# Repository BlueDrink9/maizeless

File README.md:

# Maizeless

Maizeless is a split, wireless-only, choc-spaced, diodeless mechanical keyboard, for use with the much-cheaper nice!nano clone, the [SuperMini nrf52840](https://wiki.icbbuy.com/doku.php?id=developmentboard:nrf52840).

## Lineage

Maizeless is closely related to the [Corne](https://github.com/foostan/crkbd), but without the maze of a row and column diodes (hence the name). Probably the closest description of it is a wireless [Cantor](https://github.com/diepala/cantor) (AirCantor, if you will?), or a diodeless [Swept Corne](https://github.com/AYM1607/swept-crkbd).

Going from matrix+diodes to direct pin was only possible with the extra 3 pins of the nice!nano (and clones) and giving up the TRRS pin, so this board is wireless only.

Genealogically speaking, it is forked from the [temper](https://github.com/raeedcho/temper), owing its starting shape and schematic to those pcb files. 

## Features

- 42-key split keyboard with 3 rows x 6 columns + 3 thumb keys per half 
- No diodes
- Kailh choc spacing
- Sweep-like column stagger (with pinky columns 2 mm lower, like chocofi) with Corne-like thumb cluster
- Reversible PCB (so one design can be used for both halves)
- Intended to be used with [SuperMini nrf52840](https://wiki.icbbuy.com/doku.php?id=developmentboard:nrf52840)
- Uses a dirt-cheap 3-pin [SS12D00 SPDT power switch](https://vimex.com/switches/techdocs/SS12D00-tech.pdf), of which dozens of cheap clones are available on aliexpress.
- Includes pads for battery wires on the keyboard shield PCB, and through-holes if you prefer to solder that way.
- Easy and cheap to assemble, no soldering diodes and only through-hole
  soldering.
- (non-feature) - awkward battery positioning, and no easy JST plug spot for the battery. Not a big deal, just a heads up if you care, but I figure if you're here you're happy desoldering two wires to remove a battery. The off-switch will keep the power disconnected when not in use/travelling, anyway.
- Trivial to alter the PCB design for:
  * 5 columns
  * use real nice!nanos (the 3 extra pins are in a sliiightly different position compared to the supermini).
  * Kailh hotswap sockets in the PCB design, if you'd rather solder those to pads instead of direct through-hole soldering switches.

## Bill of Materials

- PCB x2
- 2x SuperMini nrf52840 microcontrollers
- 2x LiPo batteries (see nice!nano documentation for suggestions)
- 2x SS12D00 SPDT switches
- 42x Kailh choc v1 switches
- 42x Choc v1 keycaps
- (optional) MCU socket (more of a hassle than usual because we're
  using the extra 3 pins):
  - 4x Mill-Max 310 series machine sockets
  - 54x Mill-Max pins for socketing microcontrollers
- (optional) 2x Panasonic miniature momentary button switches  (for convenient reset buttons)

## Assembly

Assembly of this keyboard requires soldering the jumpers on the front-side of each PCB (underneath the microcontrollers). Past this, the assembly of this keyboard is similar to that of many other split wireless keyboards--there are many guides online to help. Briefly, the full list of steps includes:

- Solder the jumpers underneath the microcontrollers
- On PCB back:
  - Solder the diodes (ensuring diodes are oriented correctly--check diode schematic to match orientation to PCB)
  - Solder the switch sockets
- On PCB front:
  - Solder reset switch
  - Solder power switch
  - [Socket microcontroller](https://docs.splitkb.com/hc/en-us/articles/360011263059-How-do-I-socket-a-microcontroller-):
    - Solder sockets into PCB
    - Place masking tape (to divert solder from socket for next soldering step)
    - Insert Mill-Max pins or diode legs
    - Place microcontroller (blank side up)
    - Solder pins to microcontroller
    - Carefully remove microcontroller
    - Remove tape
  - (optional) socket nice!view displays (same procedure as socketing microcontroller)
  - *Carefully* solder battery wires to pads (ensuring wires don't short together--I used masking tape to secure wires)
  - (optional) For back plate: attach standoffs to PCB with screws
  - Press choc switches into sockets (ensuring that switch legs make it into the sockets and don't bend out of the way)
  - Place keycaps
  - Reseat microcontroller
- (optional) slide back plate onto standoffs and secure with screws
- (recommended) desolder SuperMini resistor that drains current for
  VCC output (since we aren't using it for LEDs).

## Firmware

This keyboard uses [ZMK firmware](https://zmk.dev), which allows for configuration through GitHub Actions. An example configuration repository is [here](https://github.com/raeedcho/temper-zmk-config.git).

## Resources

These KiCAD libraries have elements adapted for use in this design.
It is possible that kbd, marbastlib and keyswitches.pretty need to be installed
as global KiCAD libraries, although I've tried to embed everything
necessary as project files.

- [kbd](https://github.com/foostan/kbd) - This library, by foostan, the designer of the popular Corne keyboard, provides useful schematic symbols and footprints
- [keyswitches.pretty](https://github.com/daprice/keyswitches.pretty) - library of switch footprints--especially useful for reversible PCBs.
- [marbastlib](https://github.com/ebastler/marbastlib) - "A library
  collecting MX and Choc style footprints, as well as various other
  parts used to design custom keyboards."
- [supermini-nrf52840-kicad](https://github.com/bluedrink9/supemini-nrf52840-kicad) - Contains reversible PCB footprints for SuperMini pinout

## Similar keyboards

There are many similar keyboards to this one. Here are some of the
closest; the original temper repo has a more complete list.

- [Corne/crkbd](https://github.com/foostan/crkbd) - A popular column stagger, 42-key split keyboard with many variants
- [Cornish Zen](https://lowprokb.ca/collections/keyboards/products/corne-ish-zen) - A low-profile wireless redesign of the Corne with choc spacing, screens, and an aluminum case
- [Fifi](https://github.com/raychengy/fifi_split_keeb) - 36-key split keyboard. Basically an MX Ferris Sweep with a Corne thumb cluster
- [Chocofi](https://github.com/pashutk/chocofi) - Choc version of the Fifi. Stagger is like the Kyria and Ferris keyboards, but with the pinky column 2mm lower. The keyboard this repository was based on.
- [temper](https://github.com/raeedcho/temper) - chocofi-based
  wireless-only split keyboard
- [Ferris Sweep](https://github.com/davidphilipbarr/Sweep) - Redesign of the Ferris for ProMicro MCU pinout, which also allows for a diodeless build. Many variations.
- [Swept Corne](https://github.com/AYM1607/swept-crkbd) - A wireless-only mix between the Corne and Ferris Sweep--basically a choc-spaced Corne with the Kyria pinky stagger (or alternatively a choc-spaced Kyria with a Corne thumb cluster)
- [Cantor](https://github.com/diepala/cantor) - 42 key wired
  keyboard, also diodeless thanks to the bountiful pins of the
  Blackpill.

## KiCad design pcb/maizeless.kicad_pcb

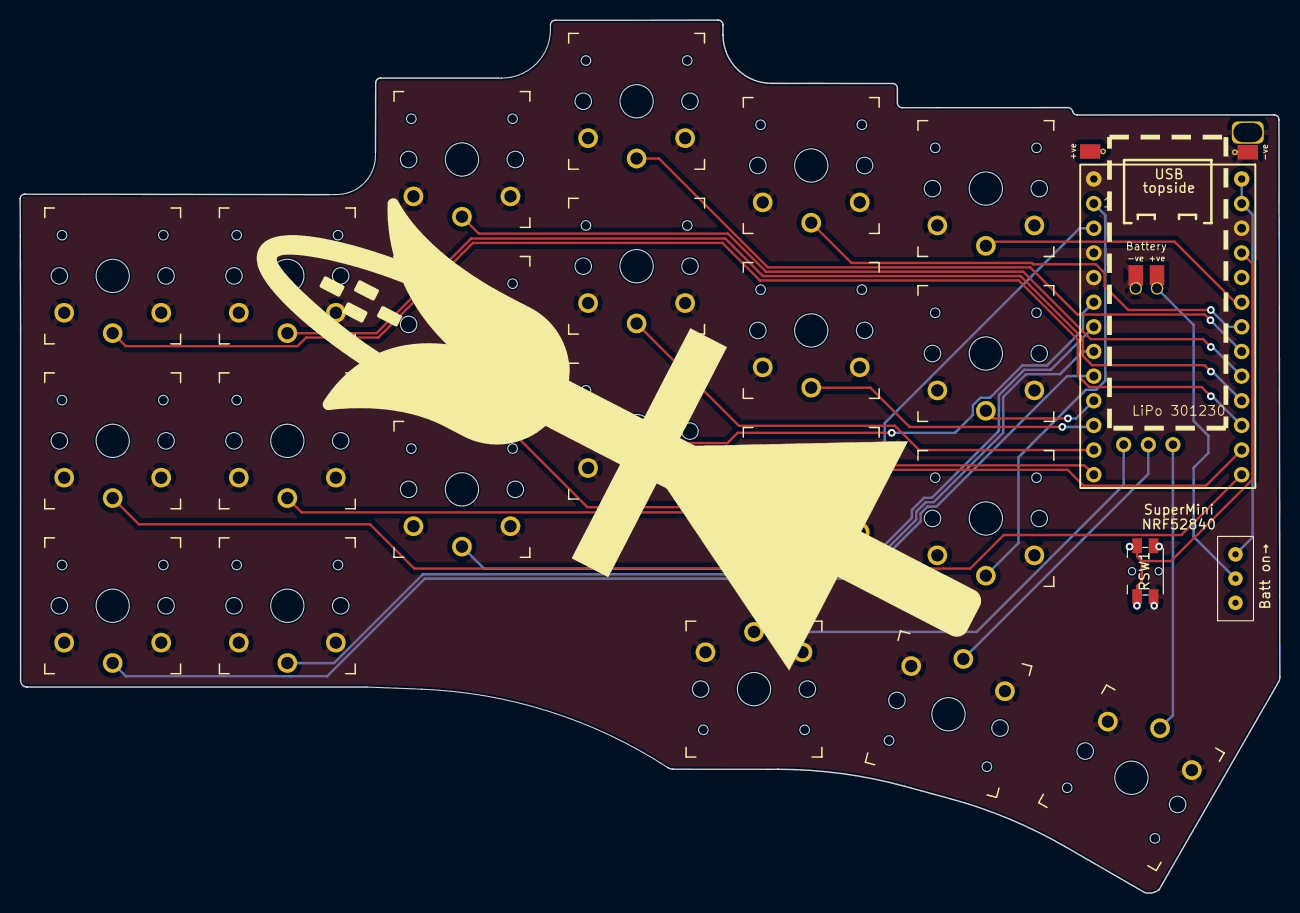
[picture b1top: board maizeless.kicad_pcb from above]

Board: 2 copper layers, 129.8 x 90.0 mm, 27 parts (0 on the bottom side), 25 nets.

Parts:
BT1, BT1#2, BT1#3: Battery_Cell; Battery_pads_reversible
PWR_SW1: SW_SPDT; SW_Slide_SPDT_SS12D00
RSW1: SW_PUSH; Panasonic_EVQPUL_EVQPUC_reversible
SW1, SW2, SW3, SW4, SW5, SW6, SW7, SW8, SW9, SW10, SW11, SW12, SW13, SW14, SW15, SW16, SW17, SW18, SW19, SW20, SW21: SW_PUSH; SW_PG1350_reversible
u1: nice_nano; SuperMini NRF52840

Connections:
GND: BT1#2.2 (-), BT1#3.2 (-), RSW1.2, SW1.2, SW2.2, SW3.2, SW4.2, SW5.2, SW6.2, SW7.2, SW8.2, SW9.2, SW10.2, SW11.2, SW12.2, SW13.2, SW14.2, SW15.2, SW16.2, SW17.2, SW18.2, SW19.2, SW20.2, SW21.2, u1.3 (GND), u1.4 (GND), u1.14 (GND), u1.28 (GND)
unnamed: BT1#3.1 (+), PWR_SW1.2 (B)
key1: SW1.1, u1.22 (P1.11-LF)
key2: SW2.1, u1.21 (P1.13-LF)
key3: SW3.1, u1.20 (P1.15-LF)
key4: SW4.1, u1.19 (P0.02-LF)
key5: SW5.1, u1.18 (P0.29-LF)
key6: SW6.1, u1.17 (P0.31-LF)
key7: SW7.1, u1.24 (P0.09-LF)
key8: SW8.1, u1.23 (P0-10-LF)
key9: SW9.1, u1.12 (P1.06-LF)
key10: SW10.1, u1.11 (P1.04-LF)
key11: SW11.1, u1.10 (P0.11)
key12: SW12.1, u1.9 (P1.00)
key13: SW13.1, u1.8 (P0.24)
key14: SW14.1, u1.7 (P0.22)
key15: SW15.1, u1.6 (P0.20)
key16: SW16.1, u1.5 (P0.17)
key17: SW17.1, u1.2 (P0.08)
key18: SW18.1, u1.1 (P0.06)
reset: RSW1.1, u1.15 (RST)
thumb1: SW19.1, u1.25 (P1.01-LF)
thumb2: SW20.1, u1.26 (P1.02-LF)
thumb3: SW21.1, u1.27 (P1-07-LF)
vbat: PWR_SW1.3 (C), u1.13 (BAT+), u1.29 (BAT+)

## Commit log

2024-03-24 Change to supermini and alter name and shape
2024-03-24 Remove images and case
2024-03-24 Route
2024-03-24 Shift thumb3, remove switch labels
2024-03-24 Route and fix DRC errors
2024-03-24 Add logo
2024-03-24 remove redundant trace
2024-03-24 Address fab constraints
2024-03-24 Replace blind vias with thru beside pad
2024-03-24 Make battery thru-holes 1 mm
    In case I want to solder wires through rather than on
2024-03-25 Re-route for nicer looking traces; fix missing ground
2024-03-26 Extra battery pads in case I want to keep everything on top
2024-03-26 Fix ERC rules by setting gnd pins to input
2024-04-07 Tweak readme
